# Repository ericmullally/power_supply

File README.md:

# power_supply

Simple build for a Breadboard power supply.

## Major hardware
* STM32F401 MCU.
* VIM-878-336640 LCD.
* BU91797MUF-ME2 LCd Driver.
* tps63070 Voltage regulator.

## Details 
The power supply is meant to provide voltage in the 1V - 8V DC range to a user breadboard.
It uses either a USB type B connection or a power jack connector not to exceed 16V.  The 
tps63070 is rated to supply up to 2 amps of current depending on the input and output 
voltages (see Docs->ICs for datasheet). 

## Documents 
Attached is the basic code written for the STM32Ide version 1.11 using the HAL library.
The driver for the LCD display, along with the schematics for the board (for KiCad) and relevant datasheets. 

## License
This repository is licensed under The MIT License.

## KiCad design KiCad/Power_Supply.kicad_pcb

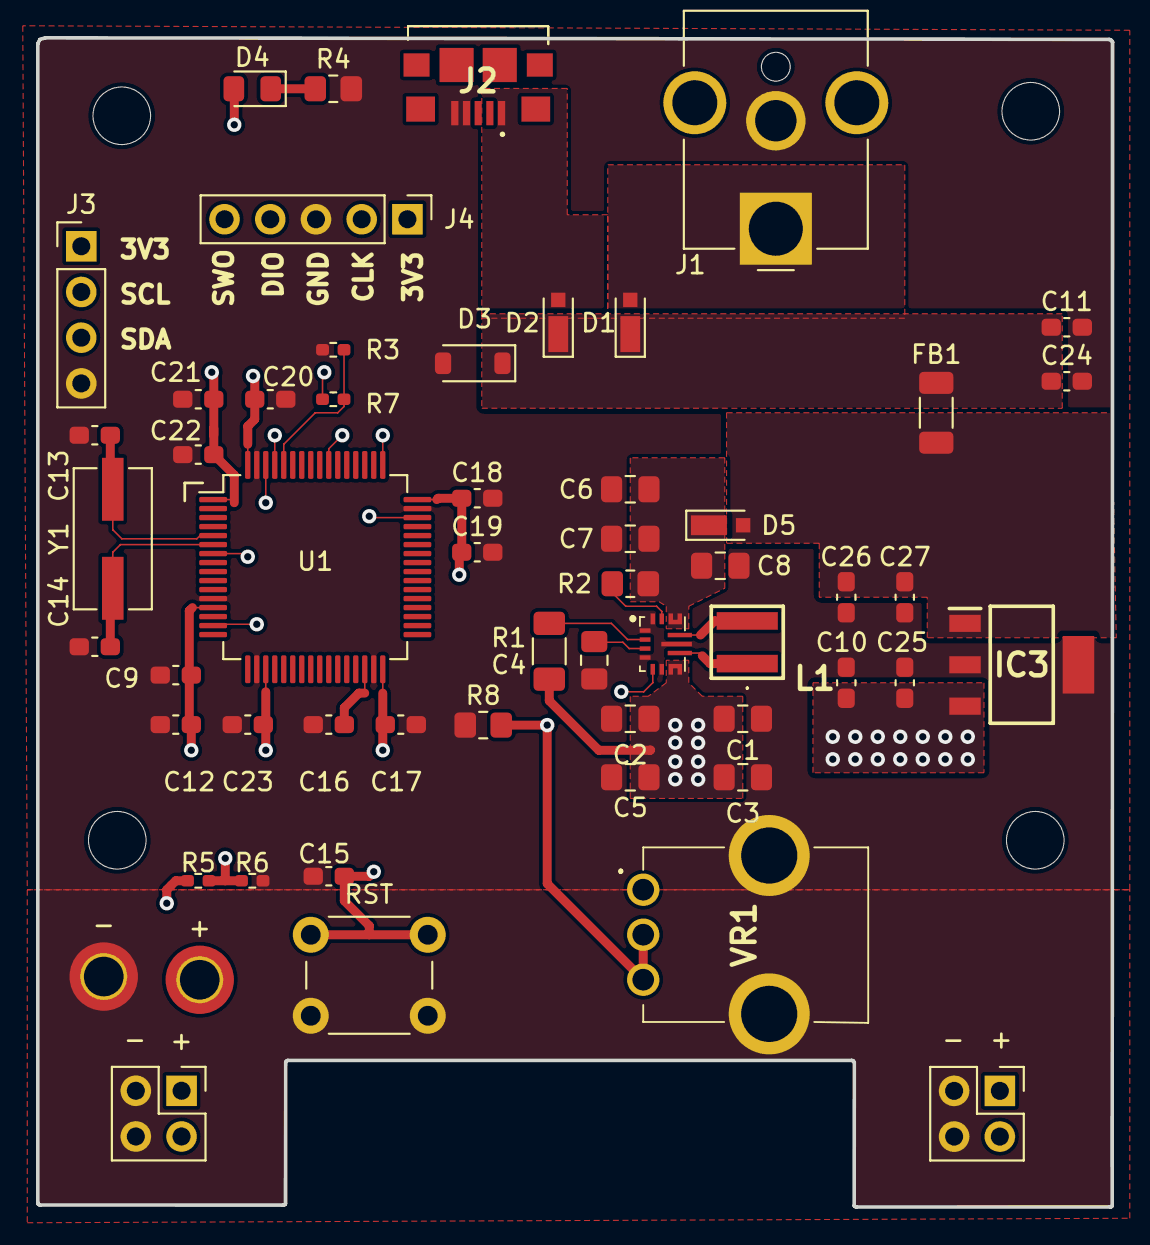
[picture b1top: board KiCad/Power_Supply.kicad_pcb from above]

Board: 4 copper layers, 59.7 x 65.0 mm, 60 parts (0 on the bottom side), 26 nets.

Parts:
+: BTM_OUT; PinHeader_2x02_P2.54mm_Vertical
+#2: Testing; MountingHole_2.2mm_M2_DIN965_Pad_TopOnly
-: Testing; MountingHole_2.2mm_M2_DIN965_Pad_TopOnly
C1, C2, C3: 22uF; C_0805_2012Metric_Pad1.18x1.45mm_HandSolder
C4: 100nF; C_0805_2012Metric_Pad1.18x1.45mm_HandSolder
C5, C6, C7, C8: 10uF; C_0805_2012Metric_Pad1.18x1.45mm_HandSolder
C9, C15, C17, C18, C19, C20, C21, C22: 100nF; C_0603_1608Metric_Pad1.08x0.95mm_HandSolder
C10, C11, C12, C24, C26: 1uF; C_0603_1608Metric_Pad1.08x0.95mm_HandSolder
C13, C14: 16pF; C_0603_1608Metric_Pad1.08x0.95mm_HandSolder
C16, C23: 4.7uF; C_0603_1608Metric_Pad1.08x0.95mm_HandSolder
C25, C27: .1uF; C_0603_1608Metric_Pad1.08x0.95mm_HandSolder
D1, D2, D5: D_Schottky; D_MicroSMP_AK
D3: 30V+; D_SOD-123
D4: Green_Led; LED_0805_2012Metric_Pad1.15x1.40mm_HandSolder
FB1: FerriteBead; L_1206_3216Metric_Pad1.22x1.90mm_HandSolder
H1, H2, H3, H4: MountingHole; MountingHole_3.2mm_M3
IC1: TPS63070RNMR; TPS630701RNMR
IC3: MCP1754ST-3302E_DB
J1: Jack-DC; BarrelJack_CUI_PJ-063AH_Horizontal_CircularHoles
J2: USB_B; 21745072
J3: LCD_connector; PinHeader_1x04_P2.54mm_Vertical
J4: SWD; PinHeader_1x05_P2.54mm_Vertical
J5: TOP_OUT; PinHeader_2x02_P2.54mm_Vertical
L1: XFL4020-152MEC; XFL4020152MEC
R1: 100K; R_1206_3216Metric_Pad1.30x1.75mm_HandSolder
R2: 10k; R_0805_2012Metric_Pad1.20x1.40mm_HandSolder
R3, R5, R7: 1K; R_0402_1005Metric_Pad0.72x0.64mm_HandSolder
R4: 165; R_0805_2012Metric_Pad1.20x1.40mm_HandSolder
R6: 500; R_0402_1005Metric_Pad0.72x0.64mm_HandSolder
R8: 2K; R_0805_2012Metric_Pad1.20x1.40mm_HandSolder
RST: NRST; SW_PUSH_6mm_H4.3mm
U1: STM32F401RBTx; LQFP-64_10x10mm_P0.5mm
VR1: PTV09A-1015U-B203; PTV09A1015UB203
Y1: Crystal; Crystal_SMD_ECS_CSM3X-2Pin_7.6x4.1mm

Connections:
+3.3V: C9.2, C10.1, C12.2, C17.1, C18.1, C19.1, C20.1, C21.1, C22.1, C23.1, C25.1, D4.2 (A), IC3.3 (VOUT), J3.1, J4.1, R7.1, U1.1 (VBAT), U1.13 (VREF+), U1.19 (VDD), U1.32 (VDD), U1.48 (VDD), U1.64 (VDD)
/BOOT: R3.2, R7.2, U1.60 (BOOT0)
/MCU_POWER/JACK_OUT: D1.2 (A), J1.1
/MCU_POWER/USB_OUT: D2.2 (A), J2.1 (VBUS)
/NRST: C15.2, RST.2, U1.7 (NRST)
/Output_circuitry/EN: IC1.14 (EN), R2.1
/Output_circuitry/L1: IC1.9 (L2), L1.1
/Output_circuitry/L2: IC1.11 (L1), L1.2
/Output_circuitry/PG: IC1.2 (PG), R1.2
/Output_circuitry/VIN: C6.1, C7.1, C8.1, D5.1 (K), IC1.12 (VIN_1), IC1.13 (VIN_2), IC1.16, R2.2
/Output_circuitry/Vaux: C4.2, IC1.3 (VAUX)
/VCAP: C16.2, U1.30 (VCAP1)
ADC: +.1, +.2, +#2.1, C1.1, C2.1, C3.1, C5.1, IC1.7 (VOUT_1), IC1.8 (VOUT_2), IC1.17, J5.1, J5.2, R1.1, R5.1, VR1.1 (CCW)
CW: IC1.5 (FB), R8.2, VR1.2 (WIPER), VR1.3 (CW)
GND: +.3, +.4, -.1, C1.2, C2.2, C3.2, C4.1, C5.2, C6.2, C7.2, C8.2, C9.1, C10.2, C11.2, C12.1, C13.1, C14.1, C15.1, C16.1, C17.2, C18.2, C19.2, C20.2, C21.2, C22.2, C23.2, C24.2, C25.2, C26.2, C27.2, D3.2 (A), IC1.1 (PS/S), IC1.4 (GND), IC1.6 (FB2), IC1.10 (PGND), IC1.15 (VSEL), IC3.2 (GND_1), IC3.4 (GND_2), J1.2, J2.4 (GND), J2.5 (Shield), J3.4, J4.3, J5.3, J5.4, R3.1, R4.2, R6.1, R8.1, RST.1, U1.12 (VSSA), U1.18 (VSS), U1.31 (VSS), U1.47 (VSS), U1.63 (VSS), VR1.MH1, VR1.MH2
Main_in: C26.1, C27.1, D5.2 (A), FB1.2, IC3.1 (VIN)
unnamed: C11.1, C24.1, D1.1 (K), D2.1 (K), D3.1 (K), FB1.1
unnamed: D4.1 (K), R4.1
unnamed: R5.2, R6.2, U1.15 (PA1)
unnamed: C13.2, U1.5 (PH0), Y1.2
unnamed: C14.2, U1.6 (PH1), Y1.1
SCL: J3.2, U1.61 (PB8)
SDA: J3.3, U1.62 (PB9)
SWCLK: J4.2, U1.49 (PA14)
SWDIO: J4.4, U1.46 (PA13)
SWO: J4.5, U1.55 (PB3)

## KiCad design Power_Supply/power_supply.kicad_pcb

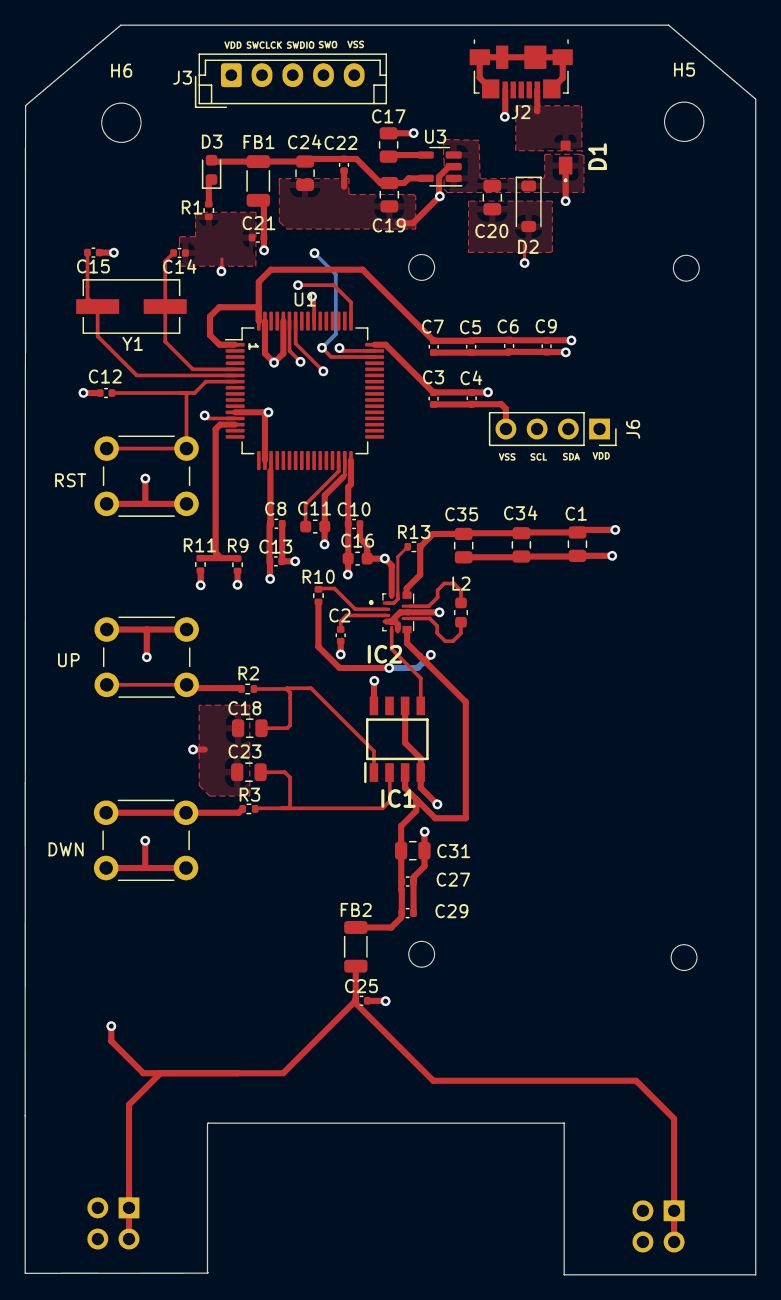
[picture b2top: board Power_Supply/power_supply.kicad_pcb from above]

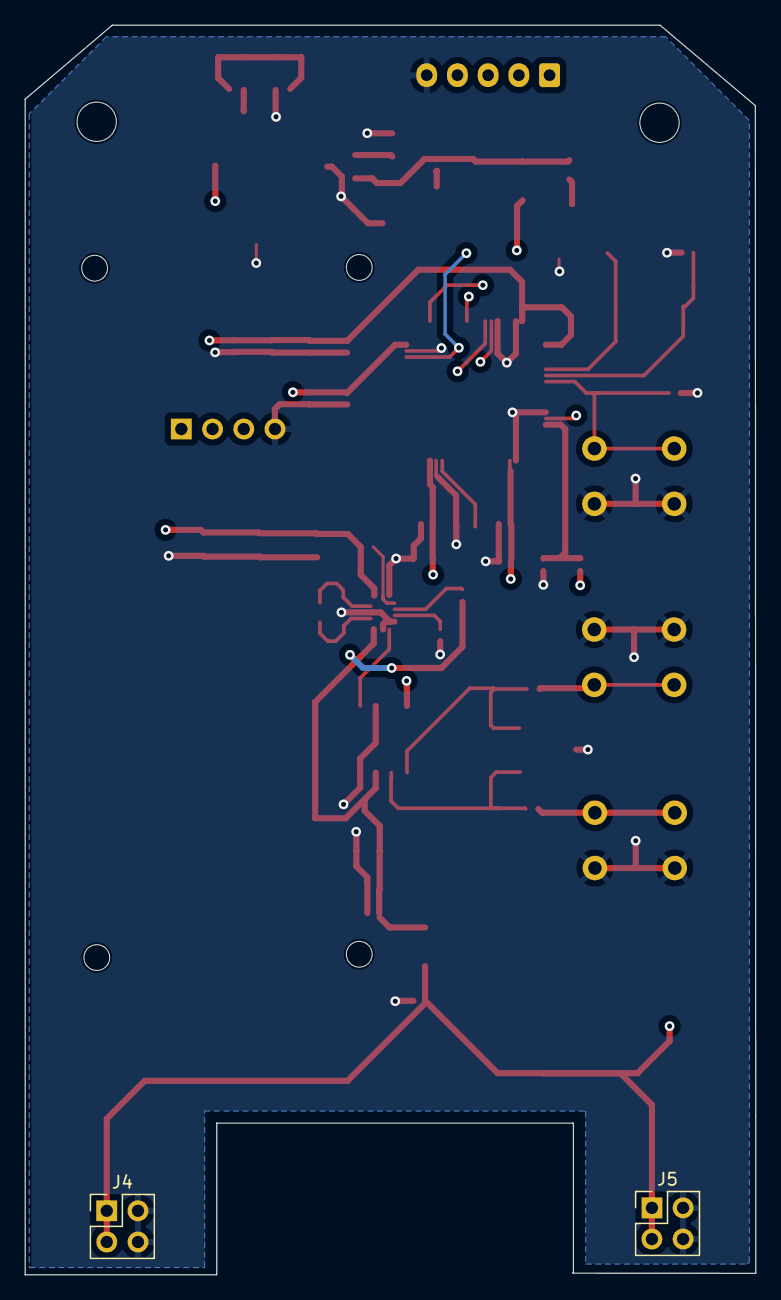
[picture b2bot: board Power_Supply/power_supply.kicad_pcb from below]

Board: 4 copper layers, 59.5 x 101.7 mm, 62 parts (2 on the bottom side), 29 nets.

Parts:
C1, C18, C19, C20, C23, C24, C31, C34, C35: 10uF; C_0805_2012Metric
C2, C3, C4, C5, C6, C7, C8, C9, C10, C12, C13: 100nF; C_0402_1005Metric
C11, C16: 4uF7; C_0603_1608Metric
C14, C15: 16pF; C_0402_1005Metric
C17: 10nF; C_0805_2012Metric
C21, C22, C25, C27, C29: 22uF; C_0402_1005Metric
D1: D_Schottky; RB168VWM30TR
D2: D_Zener; D_SOD-123
D3: LED; LED_0603_1608Metric
DWN: SW_Push; SW_PUSH_6mm_H7.3mm
FB1, FB2: FerriteBead; L_1206_3216Metric
H1, H2, H3, H4: MountingHole; MountingHole_2.1mm
H5, H6: MountingHole; MountingHole_3.2mm_M3
IC1: ISL23511WFB8Z; SOIC127P600X175-8N
IC2: TPS63070RNMR; TPS630701RNMR
J2: USB_B_Mini; USB_Micro-B_Molex_47346-0001
J3: Conn_01x05_Pin; JST_EH_B5B-EH-A_1x05_P2.50mm_Vertical
J4, J5: Conn_02x02_Odd_Even; PinHeader_2x02_P2.54mm_Vertical
J6: Conn_01x04_Socket; PinSocket_1x04_P2.54mm_Vertical
L2: 1.5uH; L_0603_1608Metric
R1: 200; R_0402_1005Metric
R2, R3, R9, R11: 100; R_0402_1005Metric
R10: 100K; R_0402_1005Metric
R13: 10K; R_0402_1005Metric
RST: SW_Push; SW_PUSH_6mm_H7.3mm
U1: STM32F401RBTx; LQFP-64_10x10mm_P0.5mm
U3: LD3985G18R_TSOT23; TSOT-23-5
UP: SW_Push; SW_PUSH_6mm_H7.3mm
Y1: 26MHz; Crystal_SMD_ECS_CSM3X-2Pin_7.6x4.1mm

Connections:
+3.3V: C3.1, C4.1, C5.1, C6.1, C7.1, C8.1, C9.1, C10.1, C13.1, C16.1, C21.1, FB1.1, IC1.8 (VCC), J3.1, J6.1, U1.1 (VBAT), U1.13 (VREF+), U1.19 (VDD), U1.32 (VDD), U1.48 (VDD), U1.64 (VDD)
/Board_PWR/usb_out: D1.2 (A), J2.1 (VBUS)
/Crystal_in: C14.2, U1.5 (PH0), Y1.2
/Crystal_out: C15.2, U1.6 (PH1), Y1.1
/Main_Supply/PG: IC2.2 (PG), R10.1
/Main_Supply/Pot_dwn: C23.1, IC1.2 (~PD), R3.2
/Main_Supply/Pot_up: C18.1, IC1.1 (~PU), R2.2
/Main_Supply/switch_L1: IC2.11 (L1), L2.2
/Main_Supply/switch_L2: IC2.9 (L2), L2.1
/Nrst: C12.1, RST.2, U1.7 (NRST)
/V_Cap: C11.1, U1.30 (VCAP1)
ADC1: R9.2, R11.2, U1.14 (PA0)
FB: IC1.5 (RW), IC2.5 (FB)
GND: C1.2, C2.1, C3.2, C4.2, C5.2, C6.2, C7.2, C8.2, C9.2, C10.2, C11.2, C12.2, C13.2, C14.1, C15.1, C16.2, C17.1, C18.2, C19.1, C20.1, C21.2, C22.2, C23.2, C24.2, C25.2, C27.2, C29.2, C31.2, C34.2, C35.2, D2.2 (A), DWN.1, IC1.4 (VSS), IC1.6 (RL), IC2.4 (GND), IC2.6 (FB2), IC2.10 (PGND), IC2.15 (VSEL), J2.5 (GND), J3.5, J4.2, J4.4, J5.2, J5.4, J6.4, R1.2, R9.1, RST.1, U1.12 (VSSA), U1.18 (VSS), U1.31 (VSS), U1.47 (VSS), U1.60 (BOOT0), U1.63 (VSS), U3.2 (GND), UP.1
Main_Supply: C25.1, FB2.1, J4.1, J4.3, J5.1, J5.3, R11.1
unnamed: D3.1 (K), R1.1
unnamed: IC2.1 (PS/S), IC2.14 (EN), R13.1
unnamed: C2.2, IC2.3 (VAUX)
unnamed: R2.1, UP.2
unnamed: DWN.2, R3.1
unnamed: C17.2, U3.4 (BYP)
Raw: C1.1, C20.2, C34.1, C35.1, D1.1 (K), D2.1 (K), IC2.12 (VIN_1), IC2.13 (VIN_2), IC2.16, R13.2, U3.1 (VIN), U3.3 (INH)
SCL: J6.3, U1.58 (PB6)
SDA: J6.2, U1.59 (PB7)
SWCLCK: J3.2, U1.49 (PA14)
SWDIO: J3.3, U1.46 (PA13)
SWO: J3.4, U1.55 (PB3)
VOUT: C27.1, C29.1, C31.1, FB2.2, IC1.3 (RH), IC2.7 (VOUT_1), IC2.8 (VOUT_2), IC2.17, R10.2
board_out: C19.2, C22.1, C24.1, D3.2 (A), FB1.2, U3.5 (VOUT)

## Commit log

2023-03-13 initital commit
2023-03-16 Selected MCU
2023-03-16 pulling
2023-03-20 changed voltage rgeulators
2023-03-20 Schematics added
2023-03-22 added power schematic to design
2023-03-22 Adjusted the VDD supply schematic
2023-03-22 Added I2C modules
2023-03-25 Lcd files started.
2023-03-29 Defined numbers 1-9 for vim lcd
2023-03-29 Ki cad schematic update.
2023-04-04 VIM_878 updated.
2023-04-08 Schematics updated. footprint assignment and layout still needed
2023-05-16 Updated Schematic and VIM878
2023-05-25 Kicad model updated.
2023-06-05 Updated schematics. and added the correct Driver files for stm32f401
2023-06-19 Re-design of board started.
2023-06-21 Schematic redesign needs two footprints before complete.
2023-06-22 Board layout preleminary complete.
2023-06-22 Boot-0 and button layout updated.
2023-06-23 Added some notes and extra ground vias.
2023-06-28 Added hash table for LCD letters
2023-08-02 Starting revision 1.1
2023-08-16 pushing ofr system reset
2023-10-04 Replaced pot.
2023-11-14 changed to hal
2023-12-11 Create LICENSE
2024-01-06 Removed unused LCD Docs
